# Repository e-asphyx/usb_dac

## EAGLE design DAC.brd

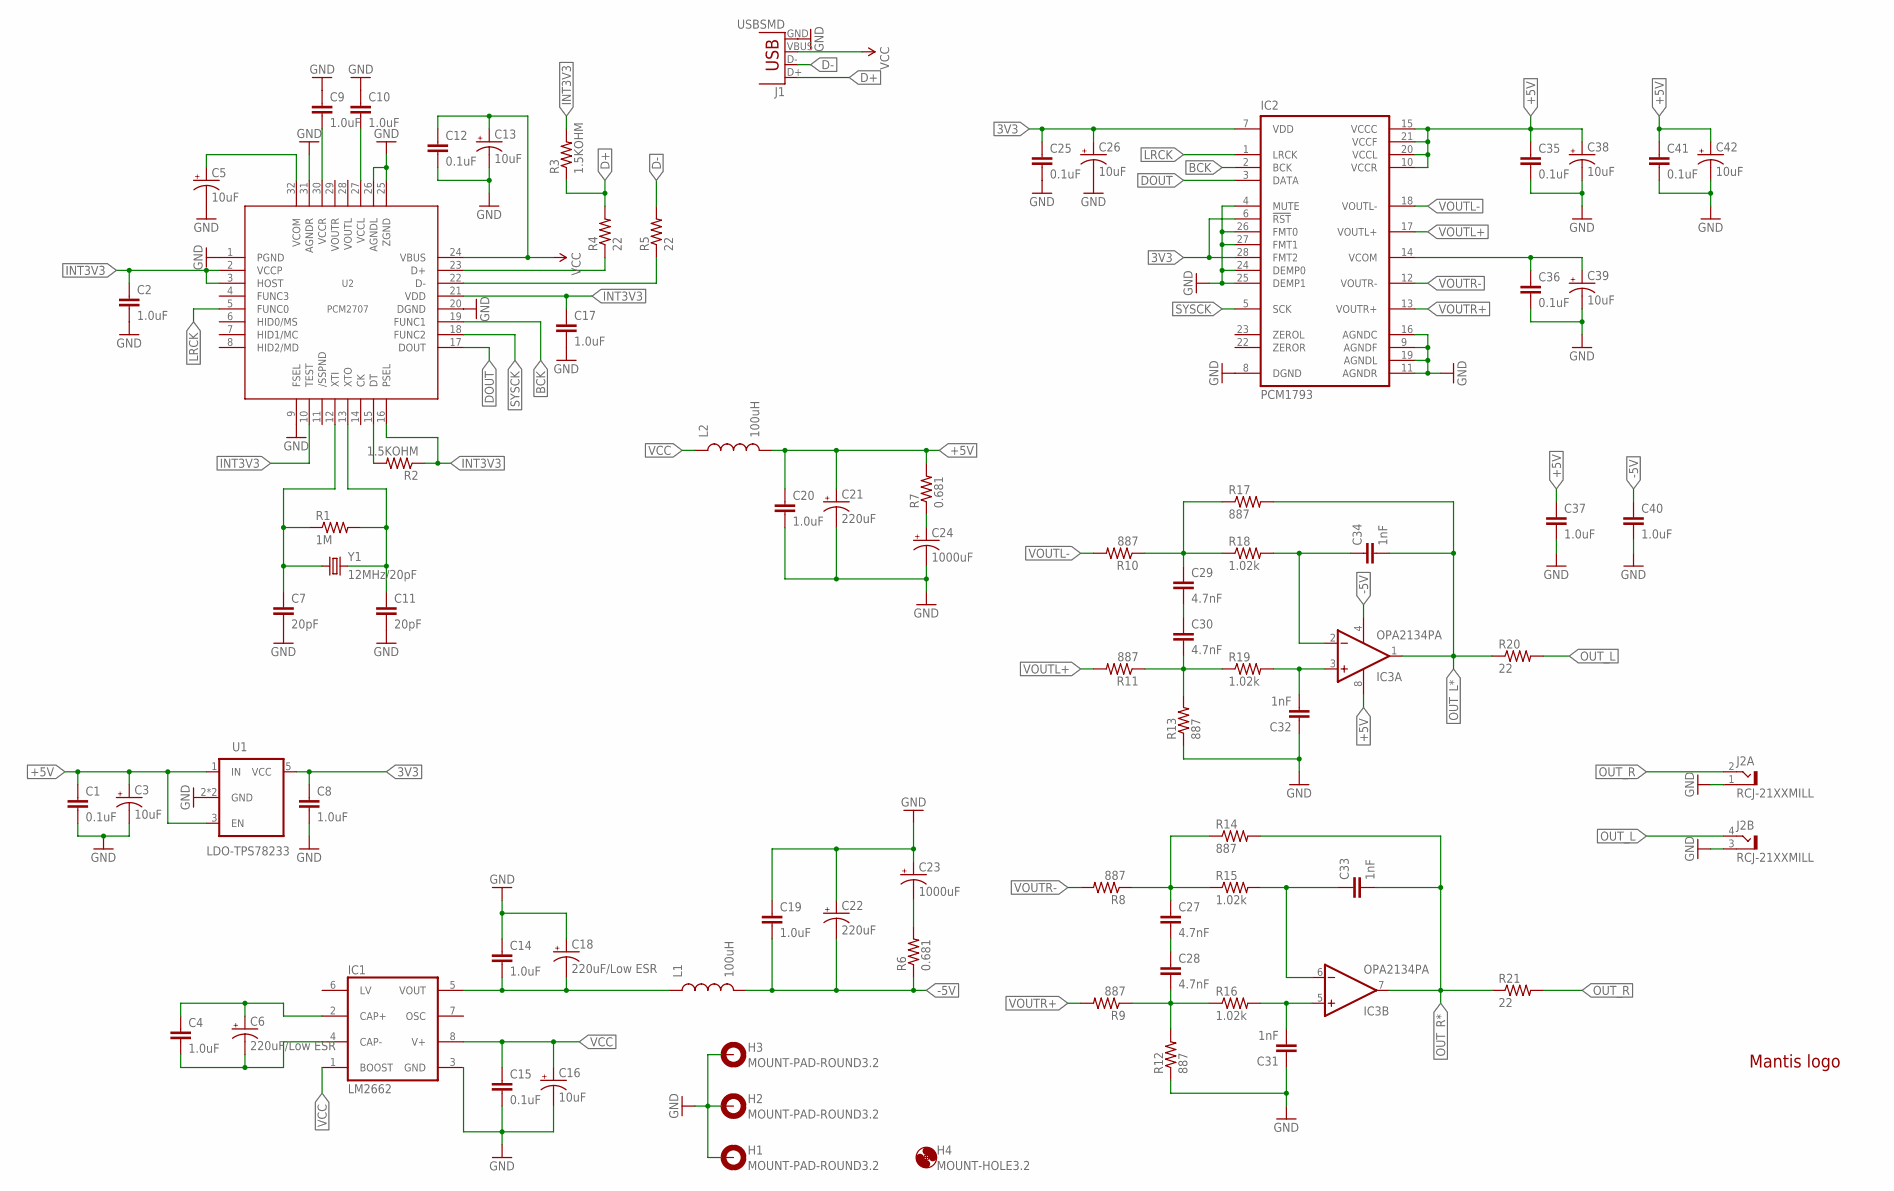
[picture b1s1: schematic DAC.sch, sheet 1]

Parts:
C1, C12, C15, C25, C35, C36, C41: 0.1uF; 0603-CAP
C2, C4, C9, C10, C14, C17, C19, C20, C37, C40: 1.0uF; 0603-CAP
C3, C5, C13, C16, C26, C38, C39, C42: 10uF; CPOL-RADIAL-10UF-25V
C6, C18: 220uF/Low ESR; CPOL-RADIAL-8/3.5
C7, C11: 20pF; 0603-CAP
C8: 1.0uF; 0805-CAP
C21, C22: 220uF; CPOL-RADIAL-8/3.5
C23, C24: 1000uF; CPOL-RADIAL-1000UF-25V
C27, C28, C29, C30: 4.7nF; C5B4.5
C31, C32, C33, C34: 1nF; C5B2.5
H1, H2, H3: MOUNT-PAD-ROUND3.2; 3,2-PAD
H4: MOUNT-HOLE3.2; 3,2
IC1: LM2662; SO08
IC2: PCM1793; SSOP28BU
IC3: OPA2134PA; DIL08
J1: USBSMD; USB-MINIB
J2: RCJ-21XXMILL; RCJ-21-MILL
L1, L2: 100uH; SRN6045; MOUSER_ID 652-SRN6045-101M
LOGO1: LOGO-MANTIS
R1: 1M; 0603-RES
R2, R3: 1.5KOHM; 0603
R4, R5: 22; 0603-RES
R6, R7: 0.681; 0603-RES
R8, R9, R10, R11, R12, R13, R14, R17: 887; AXIAL-0.4
R15, R16, R18, R19: 1.02k; AXIAL-0.4
R20, R21: 22; AXIAL-0.4
U1: LDO-TPS78233; SOT23-5
U2: PCM2707; TQFP32-08
Y1: 12MHz/20pF; HC49US; MOUSER_ID 73-XT49S1200-20

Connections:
3V3: C8.1, C25.1, C26.1 (+), IC2.6 (!RST), IC2.7 (VDD), IC2.28 (FMT2), U1.5 (VCC)
+5V: C1.1, C3.1 (+), C20.1, C21.1 (+), C35.1, C37.1, C38.1 (+), C41.1, C42.1 (+), IC2.10 (VCCR), IC2.15 (VCCC), IC2.20 (VCCL), IC2.21 (VCCF), IC3.8 (V+), L2.2, R7.2, U1.1 (IN), U1.3 (EN); also elsewhere on the board
-5V: C19.2, C22.2 (-), C40.1, IC3.4 (V-), L1.2, R6.1; also elsewhere on the board
BCK: IC2.2 (BCK), U2.19 (FUNC1)
D+: J1.D+, R3.1, R4.2
D+*: R4.1, U2.23 (D+)
D-: J1.D-, R5.2
D-*: R5.1, U2.22 (D-)
DOUT: IC2.3 (DATA), U2.17 (DOUT)
GND: C1.2, C2.2, C3.2 (-), C5.2 (-), C7.2, C8.2, C9.1, C10.1, C11.2, C12.2, C13.2 (-), C14.1, C15.2, C16.2 (-), C17.2, C18.1 (+), C19.1, C20.2, C21.2 (-), C22.1 (+), C23.+, C24.-, C25.2, C26.2 (-), C31.1, C32.1, C35.2, C36.2, C37.2, C38.2 (-), C39.2 (-), C40.2, C41.2, C42.2 (-), H1.B3,2, H2.B3,2, H3.B3,2, IC1.3 (GND), IC2.4 (MUTE), IC2.8 (DGND), IC2.9 (AGNDF), IC2.11 (AGNDR), IC2.16 (AGNDC), IC2.19 (AGNDL), IC2.24 (DEMP0), IC2.25 (DEMP1), IC2.26 (FMT0), IC2.27 (FMT1), J1.GND, J2.1 (S), J2.3 (S), R12.P$1 (1), R13.P$1 (1), U1.2 (GND), U1.4 (GND), U2.1 (PGND), U2.9 (FSEL), U2.20 (DGND), U2.25 (ZGND), U2.26 (AGNDL), U2.31 (AGNDR); also elsewhere on the board
INT3V3: C2.1, C17.1, R2.1, R3.2, U2.2 (VCCP), U2.3 (HOST), U2.10 (TEST), U2.16 (PSEL), U2.21 (VDD)
LRCK: IC2.1 (LRCK), U2.5 (FUNC0)
unnamed: R2.2, U2.15 (DT)
unnamed: C5.1 (+), U2.32 (VCOM)
unnamed: C9.2, U2.30 (VCCR)
unnamed: C10.2, U2.27 (VCCL)
unnamed: C36.1, C39.1 (+), IC2.14 (VCOM)
unnamed: C24.+, R7.1
unnamed: C14.2, C18.2 (-), IC1.5 (VOUT), L1.1
unnamed: C23.-, R6.2
unnamed: C4.1, C6.1 (+), IC1.2 (CAP+)
unnamed: C4.2, C6.2 (-), IC1.4 (CAP-)
unnamed: C29.2, C30.1
unnamed: C30.2, R11.P$1 (1), R13.P$2 (2), R19.P$1 (1)
unnamed: C29.1, R10.P$1 (1), R17.P$1 (1), R18.P$1 (1)
unnamed: C28.2, R9.P$1 (1), R12.P$2 (2), R16.P$1 (1)
unnamed: C27.1, R8.P$1 (1), R14.P$1 (1), R15.P$1 (1)
unnamed: C27.2, C28.1
OPL+: C32.2, IC3.3 (+IN), R19.P$2 (2)
OPL-: C34.1, IC3.2 (-IN), R18.P$2 (2)
OPR+: C31.2, IC3.5 (+IN), R16.P$2 (2)
OPR-: C33.1, IC3.6 (-IN), R15.P$2 (2)
OUT_L: J2.4 (T), R20.P$2 (2)
OUT_L*: C34.2, IC3.1 (OUT), R17.P$2 (2), R20.P$1 (1); also elsewhere on the board
OUT_R: J2.2 (T), R21.P$2 (2)
OUT_R*: C33.2, IC3.7 (OUT), R14.P$2 (2), R21.P$1 (1); also elsewhere on the board
SYSCK: IC2.5 (SCK), U2.18 (FUNC2)
VCC: C12.1, C13.1 (+), C15.1, C16.1 (+), IC1.1 (BOOST), IC1.8 (V+), J1.VBUS, L2.1, U2.24 (VBUS)
VOUTL+: IC2.17 (VOUTL+), R11.P$2 (2)
VOUTL-: IC2.18 (VOUTL-), R10.P$2 (2)
VOUTR+: IC2.13 (VOUTR+), R9.P$2 (2)
VOUTR-: IC2.12 (VOUTR-), R8.P$2 (2)
XTI: C7.1, R1.1, U2.12 (XTI), Y1.1
XTO: C11.1, R1.2, U2.13 (XTO), Y1.2

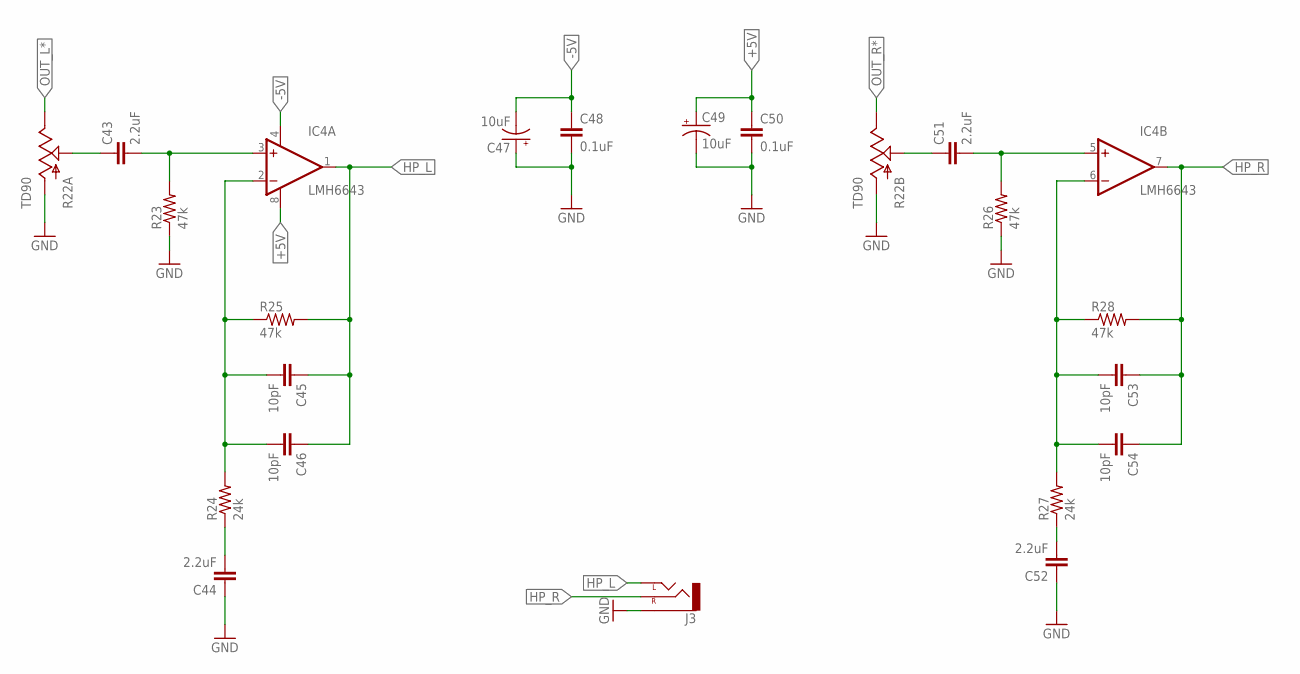
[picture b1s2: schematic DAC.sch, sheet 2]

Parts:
C43, C44, C51, C52: 2.2uF; C5B5
C45, C53: 10pF; CAP-PTH-SMALL
C46, C54: 10pF; 0603-CAP
C47, C49: 10uF; CPOL-RADIAL-10UF-25V
C48, C50: 0.1uF; 0603-CAP
IC4: LMH6643; SO08
J3: AUDIO-JACKPTH; AUDIO-JACK
R22: TD90; PTD902
R23, R25, R26, R28: 47k; AXIAL-0.4
R24, R27: 24k; AXIAL-0.4

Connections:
+5V: C49.1 (+), C50.1, IC4.8 (V+); also elsewhere on the board
-5V: C47.2 (-), C48.1, IC4.4 (V-); also elsewhere on the board
GND: C44.1, C47.1 (+), C48.2, C49.2 (-), C50.2, C52.1, J3.SLEEVE, R22.R1.1 (A), R22.R2.1 (A), R23.P$1 (1), R26.P$1 (1); also elsewhere on the board
HP_L: C45.1, C46.1, IC4.1 (OUT), J3.TIP (LEFT), R25.P$2 (2)
HP_R: C53.1, C54.1, IC4.7 (OUT), J3.RING (RIGHT), R28.P$2 (2)
unnamed: C45.2, C46.2, IC4.2 (-IN), R24.P$2 (2), R25.P$1 (1)
unnamed: C43.2, IC4.3 (+IN), R23.P$2 (2)
unnamed: C51.1, R22.R2.2 (S)
unnamed: C51.2, IC4.5 (+IN), R26.P$2 (2)
unnamed: C53.2, C54.2, IC4.6 (-IN), R27.P$2 (2), R28.P$1 (1)
unnamed: C43.1, R22.R1.2 (S)
unnamed: C52.2, R27.P$1 (1)
unnamed: C44.2, R24.P$1 (1)
OUT_L*: R22.R1.3 (E); also elsewhere on the board
OUT_R*: R22.R2.3 (E); also elsewhere on the board

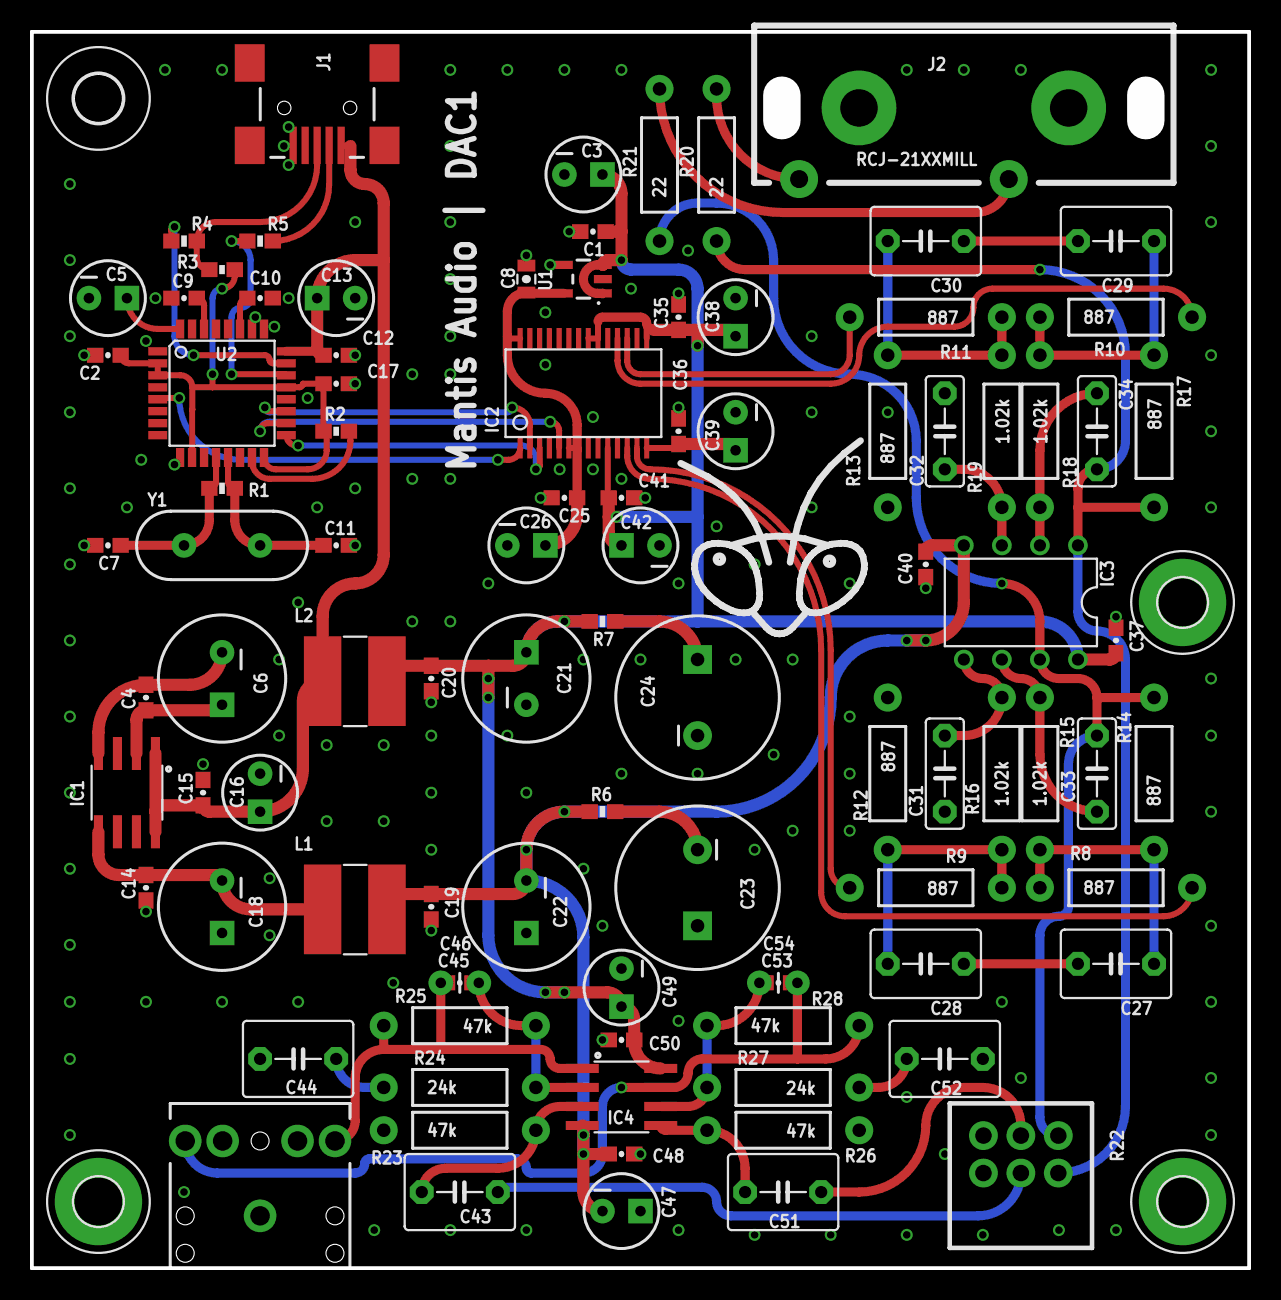
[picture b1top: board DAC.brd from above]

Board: 2 copper layers, 81.3 x 82.5 mm, 99 parts (0 on the bottom side), 54 nets.

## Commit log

2016-10-12 Initial
2016-10-12 Protection res
2016-10-13 Some packages updated
2016-10-13 Phone out
2016-10-13 Bias correction
2016-10-13 PDFs
2016-10-16 2.5mm jack was placed by mistake
2016-11-03 Phone jack position adjusted
2016-11-03 Schematics prettyfied
2016-11-04 More decoupling
2016-11-04 Caps footprint changed to more standard
2016-11-06 Power op amp is AC coupled now to avoid bias current to pass through the pot
2016-11-06 Mounting holes
2016-11-18 DRU changed
2016-11-19 PCB layout closer to guidelines
2016-11-20 Power rerouted

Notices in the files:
parts and their libraries:
SparkFun-Capacitors: Licensing: Creative Commons ShareAlike 4.0 International - https://creativecommons.org/licenses/by-sa/4.0
